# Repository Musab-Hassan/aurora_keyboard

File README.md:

# 

The Aurora keyboard is a beautifully designed fully split, wireless, ergonomic keyboard that you can build yourself.

**The full build guide can be found in `build_guide/`.**

**Key Features:**

- Bluetooth and dongle switching
- Ortholinear layout
- 65% layout (full layout with no compromises)
- Per-key RGB (if you can solder them)
- Support for any MX switches and keycaps
- OLED Screen (nice!view)
- Volume knob
- Hotswappable
- ZMK Firmware

## Repo Contents

- **STL Case Files:** 3D-printing-ready case files. You can print these without any CAD skills.
- **SLDPART Case Files:** SolidWorks case files. Modify these to create a custom layout. (Sorry, SolidWorks is the only CAD software I'm proficient in.)
- **Completed PCB Files:** Fabrication-ready routed PCB files, modifiable in KiCAD or Altium. Export them to `.gerber` files for fabrication.
- **Ergogen Files:** Ergogen configuration files used to generate the unrouted PCB. There are two separate folders since the keyboard is asymmetrical. Modify only if fundamental PCB changes are needed.

### Not Included in This Repo

- **ZMK Config:** The ZMK Firmware configuration is stored in [a separate repository](https://github.com/Musab-Hassan/zmk-config-aurora) and is not included here.

## Case Design

The Aurora keyboard uses a [plate-mounted style](https://www.keyboard.university/200-courses/keyboard-mounting-styles-4lpp7) with a top plate and a flat bottom base for each half. The PCB, microcontroller, and nice!view screens are exposed at the open ends and are covered by an acrylic piece.

Due to its ergonomic design and full 65% layout, the cases are asymmetrical, with the right side being larger than the left.

All files were designed in SolidWorks, but they can be opened and modified in other CAD/CAM software.

### Dongle and Bluetooth Switching

The case files also include a dongle case. This dongle is a third nice!nano that functions as a keyboard dongle when connected to a computer via a USB cable or USB-C male-to-male adapter. The dongle case also includes a dongle cover, which, when glued together, allows the dongle to slot into the left side of the keyboard.

The left side features a slot for the dongle. If 3-pin magnetic pogo connector is added to the pogo connector holes within both the dongle case and the left side keyboard slot, the dongle can then magnetically attach and automatically switch to Bluetooth by using the left-side battery when it slots in.

Refer to the build guide for more details.

## PCB Design

The PCB layout and unrouted PCB were generated using Ergogen. Since the two halves have different layouts, separate folders exist for each. My Ergogen skills were not sufficient to configure both in one file.

After Ergogen, the PCB was routed in KiCAD. Routed PCB files are in the `pcb` directory and are fabrication-ready. Download the zip files from the `pcb/gerber` directory and then order them for fabrication.

You can order the PCBs from manufacturers such as PCBWay or JLCPCB.

## Parts List

This list includes all external parts required, excluding the PCB and 3D-printed case files. I’ve also provided the sources where I purchased these parts. However, they may not be the cheapest or best sources. Switches and keycaps are personal preference and should be a significant part of your budget.

### Required Parts

| Part | Quantity | Where I got them from |
| --- | --- | --- |
| nice!nano | 3 (2 if no dongle) | [Typeractive](https://typeractive.xyz/products/nice-nano) |
| nice!view | 2 | [Typeractive](https://typeractive.xyz/products/nice-view) |
| 1N4148W SMD diodes | 70 | [Typeractive](https://typeractive.xyz/products/smd-diodes) |
| MX Hotswap sockets | 70 | [Amazon](https://www.amazon.ca/dp/B0972HB9GY) |
| 750 mAh Thin LiPo Battery | 2 | [Typeractive](https://typeractive.xyz/products/lithium-battery-750mah) |
| JST PH 2.0mm Battery Jack | 2 | [Typeractive](https://typeractive.xyz/products/battery-jack) |
| EC11 Encoder | 1 | [Digikey](https://www.digikey.ca/en/products/detail/alps-alpine/EC11E15244B2/19529170) |
| 0.08" Acrylic Sheet (8" x 12") | 1 | [Amazon](https://www.amazon.ca/dp/B0BK3DN8JR) |
| Alps Micro Switch | 2 | [TyperActive](https://typeractive.xyz/products/power-switch) |
| Panasonic EVQPU Reset Button | 2 | [Typeractive](https://typeractive.xyz/products/reset-button) |
| PCB Mount Stabilizers | 4 | [KBDFans](https://kbdfans.com/collections/keyboard-stabilizer/products/cherry-clip-in-stabilizer-pcb-mount) |
| MX Switches (Preference: I chose Gateron Smoothies) | 70 | [KBDFans](https://kbdfans.com/products/gateron-smoothie-linear-switch) |
| MX Keycaps (Preference: I chose PBTFans BOW) | 70 | [KBDFans](https://kbdfans.com/products/pbtfans-doubleshot-bow) |
| M2.5 6mm Countersunk Screw | 12+ | [Amazon](https://www.amazon.ca/dp/B075RCP71G) or [McMaster Carr](https://www.mcmaster.com/92010A016) |
| M2.5 8mm Hex Standoff | 8+ | [Amazon](https://www.amazon.ca/dp/B0788FR59P) or [McMaster Carr](https://www.mcmaster.com/95947A003) |
| M2.5 14mm Hex Standoff | 8+ | [Amazon](https://www.amazon.ca/dp/B0788FR59P) or [McMaster Carr](https://www.mcmaster.com/95947A009) |

### Optional But Recommended Parts

| Part | Quantity | Why | Where I got them from |
| --- | --- | --- | --- |
| 3 Pin Magnetic Pogo Connector  | 2 | Allows dongle to magnetically snap in and switch to bluetooth | [Amazon](https://www.amazon.ca/dp/B0CPJHQK2F) |
| Rubber Feet  | 8 | Prevents keyboard from slipping | [Amazon](https://www.amazon.ca/dp/B07CNQC695) |
| Neodymium Bar Magnets (60mm x 10mm x 3mm) | 2 | Allows the keyboard to magnetically snap when connected together (case plate has a slot for magnets) | [Amazon](https://www.amazon.ca/dp/B09TKMRRRC) |
| Keyboard Lube or Di-electric grease | 1 | If you want your keyboard to sound good you can lube the switches for it to sound even better (not recommended unless you are very ambitious about keyboards) | [Amazon](https://www.amazon.ca/dp/B09B9RL1QQ) |
| Neoprene Foam Sheet | 1 | Allows you to dampen keyboard sound so it sounds better. Again not recommended unless you really like dampened keyboard sounds. | [Amazon](https://www.amazon.ca/dp/B0B88BLNGQ) |
| SK6812Mini RGB LED | 70 | RGB per key backlight. Only get these if you are very experienced with SMD soldering. They are very difficult to solder by hand. There is also no support in the Aurora ZMK configuration for RGB yet as I am unable to solder them. If you do solder them you will need to add the backlight option in the ZMK config yourself for them to work. | [ClicketySplit](https://clicketysplit.ca/products/sk6812mini-programmable-rgb-led) |

### Required Tools

- Soldering iron (preferably with temperature control)
- Solder (preferably nothing larger than 0.8mm)
- Flux (optional but recommended)
- Tweezers
- FDM or Resin 3D Printer or at least access to one
- Screw driver with the appropriate bit depending on your screws

## License

GPL V3 License

Have fun with your build!

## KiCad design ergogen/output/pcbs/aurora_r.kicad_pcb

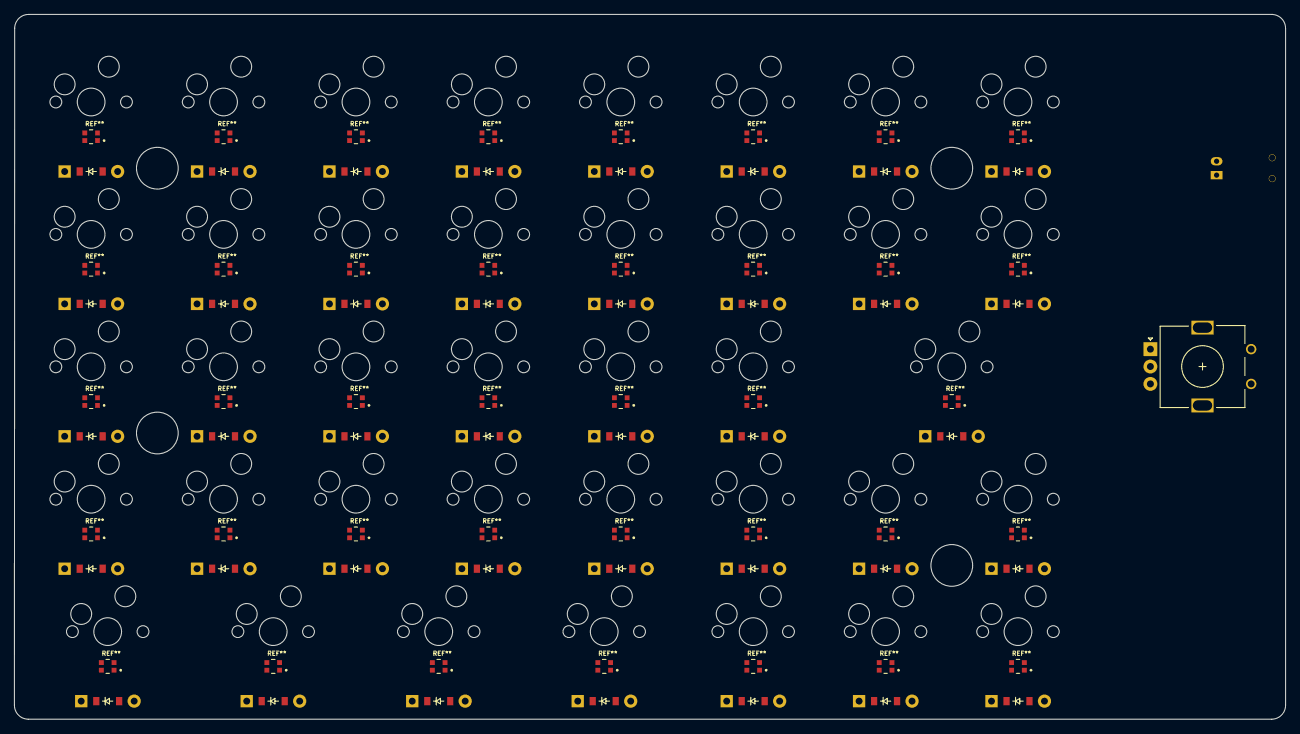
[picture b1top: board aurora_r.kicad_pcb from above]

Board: 2 copper layers, 182.9 x 101.4 mm, 79 parts (0 on the bottom side), 53 nets, no tracks yet.

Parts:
D1, D2, D3, D4, D5, D6, D7, D8, D9, D10, D11, D12, D13, D14, D15, D16, D17, D18, D19, D20, D21, D22, D23, D24, D25, D26, D27, D28, D29, D30, D31, D32, D33, D34, D35, D36, D37, D38: ComboDiode
JST1: JST_PH_S2B-PH-K_02x2.00mm_Angled
ROT1: rotary_encoder
S1, S2, S3, S4, S5, S6, S7, S8, S9, S10, S11, S12, S13, S14, S15, S16, S17, S18, S19, S20, S21, S22, S23, S24, S25, S26, S27, S28, S29, S30, S31, S32, S33, S34, S35, S36, S37, S38: MX
T1: SPDT_C128955

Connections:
BAT: JST1.1, T1.2
GND: JST1.2, ROT1.C
P01: S1.2, S2.2, S17.2, S24.2, S32.2
P02: S3.2, S4.2, S18.2, S25.2, S33.2
P03: S5.2, S6.2, S19.2, S26.2, S34.2
P04: S7.2, S8.2, S20.2, S27.2, S35.2
P05: S9.2, S10.2, S21.2, S28.2, S36.2
P06: S11.2, S12.2, S22.2, S29.2, S37.2
P07: S13.2, S14.2, S23.2, S30.2, S38.2
P08: S15.2, S16.2, S31.2
P09: D2.1, D4.1, D6.1, D8.1, D10.1, D12.1, D14.1, D16.1
P10: D1.1, D3.1, D5.1, D7.1, D9.1, D11.1, D13.1, D15.1
P11: D17.1, D18.1, D19.1, D20.1, D21.1, D22.1, D23.1
P12: D24.1, D25.1, D26.1, D27.1, D28.1, D29.1, D30.1, D31.1
P13: D32.1, D33.1, D34.1, D35.1, D36.1, D37.1, D38.1
alt_modrow: D35.2, S35.1
ctrl_modrow: D33.2, S33.1
down_arrow_modrow: D37.2, S37.1
eight_bottom: D31.2, S31.1
eight_num: D16.2, S16.1
eight_top: D15.2, S15.1
enter_home: D23.2, S23.1
five_bottom: D28.2, S28.1
five_home: D21.2, S21.1
five_num: D10.2, S10.1
five_top: D9.2, S9.1
four_bottom: D27.2, S27.1
four_home: D20.2, S20.1
four_num: D8.2, S8.1
four_top: D7.2, S7.1
left_arrow_modrow: D36.2, S36.1
one_bottom: D24.2, S24.1
one_home: D17.2, S17.1
one_num: D2.2, S2.1
one_top: D1.2, S1.1
right_arrow_modrow: D38.2, S38.1
seven_bottom: D30.2, S30.1
seven_num: D14.2, S14.1
seven_top: D13.2, S13.1
six_bottom: D29.2, S29.1
six_home: D22.2, S22.1
six_num: D12.2, S12.1
six_top: D11.2, S11.1
space_modrow: D32.2, S32.1
super_modrow: D34.2, S34.1
three_bottom: D26.2, S26.1
three_home: D19.2, S19.1
three_num: D6.2, S6.1
three_top: D5.2, S5.1
two_bottom: D25.2, S25.1
two_home: D18.2, S18.1
two_num: D4.2, S4.1
two_top: D3.2, S3.1

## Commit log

2024-10-16 Aurora left pcb completion
2024-10-16 Refine left board further
2024-10-16 Complete right PCB
2024-10-18 Add stab holes and extended base to PCB
2024-10-24 Key clearance fixes and mounting hole placement fixes
2024-10-24 Plate case
2024-10-24 Generate output CAD files
2024-10-27 Left PCB dimensioning tweaks
2024-10-27 Fixed left PCBs with routing
2024-10-27 Right PCB dimensioning tweaks
2024-11-02 Redesign left PCB board layout
2024-11-06 Left PCB pin layout fixes and full routed pcb
2024-11-21 Full redesign of right side with rotary encoder
2024-11-21 Right full routed PCB
2024-11-21 Add stab holes to PCBs
2024-12-26 Minor adjustment to left pcb
2024-12-26 Rotary encoder pinout fixes
2024-12-28 Pin changes on encoder button
2025-01-29 Remove unused package file
2025-01-29 Add License
2025-01-29 Add STL and CAD case files
2025-01-30 Add README
2025-01-30 Add more parts to README
2025-01-31 Add images to README
2025-02-01 Initial commit for build guide
2025-02-01 Logo banner in README
2025-02-01 Rename "docs" to "build_guide"
2025-02-01 Clarify a point
2025-02-01 Add Dongle Enclosure
2025-02-01 Add images to build guide
2025-02-01 Typo fix
2025-02-02 Add gerber files and clarify pcb ordering
2025-02-02 Grammatical error fixes
2026-03-05 Simplify ergogen for v2
2026-03-05 Ergogen output
2026-03-06 Fix ergogen pcb cutouts
2026-03-06 Organize pins and clean up led footprint
2026-03-06 Simplify LED rotations
